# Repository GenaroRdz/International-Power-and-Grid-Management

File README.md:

# ⚡ Design and Implementation of Mechatronic Systems: ECU Test Bench

This repository contains all the code, hardware schematics, and assets used for the class **Design and Implementation of Mechatronic Systems**. 

The core of this project is a **High-Current Load Controller (ECU Test Bench)** designed to safely simulate, control, and monitor high-power loads (12V/5A) using solid-state switching and a custom Python Graphical User Interface (GUI).

---# ⚡ Automated HIL Power & Grid Management Unit

> **Solid-State ECU Test Bench for Automotive Hardware-In-the-Loop (HIL) Validation**

This repository contains the firmware, host software, hardware schematics, and testing assets developed for the *Design and Implementation of Mechatronic Systems* engineering capstone. 

The core of this project is a **High-Current Power Management Unit (PMU)** designed to safely automate the power cycling, control, and real-time monitoring of automotive Electronic Control Units (ECUs). By replacing traditional mechanical relays and manual resets with a fully automated, VISA-compliant Python GUI and a solid-state switching matrix, this system provides a robust framework for continuous ECU stress-testing.

## 📋 System Architecture

The architecture relies on a strict separation of concerns across three layers, safely isolating the low-voltage logic control (3.3V) from the raw automotive power stage (12V) using galvanic isolation.

1. **Host Layer (PC / Python):** A robust GUI that manages serial connection watchdogs, visualizes live telemetry on an oscilloscope, and parses automation scripts (e.g., `LOOP 10`, `DELAY 100`) into single-line SCPI/VISA string commands (`*IDN?`, `ECU1_BAT ON`).
2. **Control Layer (ESP32 / MicroPython):** An asynchronous event-driven firmware (`asyncio`) that parses commands, manages GPIO logic, polls I2C sensors, and controls the SPI CAN bus simultaneously without blocking the main loop.
3. **Hardware Layer (Custom PCB):** A 12-channel power delivery matrix protecting the logic domain from automotive 12V inrush currents and inductive spikes.

## 🚀 Key Features & Core Components

* **Solid-State Power Matrix:** Independent 12V/5A control over Battery (BAT), Accessory (ACC), and Ignition (IGN) lines across 4 distinct ECU channels.
  * *Component:* P-Channel Power MOSFETs (IRF4905) driven by PC817 Optocouplers.
* **Real-Time I2C Telemetry:** Closed-loop monitoring of voltage, current, and power consumption per channel using custom bare-metal I2C drivers.
  * *Component:* INA226 digital power monitors with ultra-low 0.01Ω shunt resistors and hardware-configured I2C addresses.
* **CAN Bus Integration:** SPI-driven CAN controller integration for broadcast messaging, ECU node-health supervision, and live traffic monitoring via the GUI.
  * *Component:* MCP2515 CAN Controller + TJA1050 Transceiver.
* **Automated Sequencer:** Custom scripting engine allowing the execution of complex testing vectors (e.g. stress tests) directly from `.txt` files.

## 📂 Repository Structure

* `/Firmware`: MicroPython scripts for the ESP32 (main asynchronous loop, custom `INA226.py` and `mcp2515.py` register-level drivers, command parser).
* `/Software`: Python GUI application (Tkinter), live scope plotting, CAN monitor, and serial management.
* `/Hardware`: KiCad schematics, wiring diagrams, LTspice validation simulations (`.asc`, `.model`), and Bill of Materials (BOM).
* `/Tests`: Example sequence `.txt` files for automated stress testing (e.g., `COMPLETE Test.txt`).
* `/Docs`: Final Technical Report, architecture diagrams, and component datasheets.

## 🛠️ Setup and Installation

### 1. Hardware Assembly
Assemble the physical circuit following the schematics provided in the `/Hardware` folder.
> ⚠️ **Safety Warning:** This system handles cumulative currents capable of exceeding 15A during inrush events. Ensure the use of appropriate gauge wiring (AWG 16 minimum) for the 12V power bus, use proper thermal dissipation techniques, and include a master inline fuse & kill-switch before the MOSFET array.

### 2. Firmware (ESP32)
1. Flash the ESP32 microcontroller with the latest MicroPython firmware.
2. Upload all python scripts from the `/Firmware` folder to the board using tools like Thonny IDE or `mpremote`.
3. The board will automatically execute `main.py` on boot, initialize the SPI/I2C buses, and await serial commands at `115200` bauds.

### 3. Software (Python GUI)
The host control interface requires **Python 3.13.x**. Navigate to the software folder and install the required dependencies:

```bash
cd Software
pip install -r requirements.txt
python main.py
```
## 📋 System Architecture

The project is modularly designed, safely isolating the low-voltage logic control (3.3V) from the raw power stage (12V) using optocouplers. 

### Core Components:
* **Microcontroller:** ESP32 running MicroPython.
* **Power Switching:** P-Channel Power MOSFET (IRF4905).
* **Current/Voltage Monitoring:** INA226 (I2C) with an ultra-low shunt resistor.
* **Isolation:** PC817 Optocoupler.
* **Simulated Load:** 120 Ohms Resistors. (in total 12 Resistors ~1.2A drawn).

---

## 📂 Repository Structure

* `/firmware`: MicroPython scripts for the ESP32 (I2C sensor reading, PWM/Digital control).
* `/software`: Python GUI application for remote monitoring and control.
* `/hardware`: Circuit schematics, wiring diagrams, and LTspice simulations (`.asc`, `.model`).
* `/docs`: Final Report, technical documentation and component datasheets (INA226, IRF4905, etc.).

---

## 🛠️ Setup and Installation

### 1. Hardware Assembly
Assemble the physical circuit following the schematics provided in the `/hardware` folder. 
> ⚠️ **Safety Warning:** This system handles currents <= 5A. Ensure the use of appropriate gauge wiring (AWG 16 minimum) for the power stage and include a master kill-switch before the MOSFET array.

### 2. Firmware (ESP32)
Flash the ESP32 with the latest MicroPython firmware. Upload the scripts from the `/firmware` folder to the board using tools like Thonny IDE or `mpremote`.

### 3. Software (Python GUI)
The control interface requires **Python 3.13.xx**. Navigate to the software folder and install the required dependencies:

```bash
cd software
pip install -r requirements.txt
python main.py

Authors:
Genaro Rodríguez Garza - A00831640 
Juan Pablo Carrasco Ferra Martínez - A01252910 
Eduardo de la Rosa Flores - A01039969 
Kleber Andres Molina Yepez - A00838725 
Jose Joaquin Rodriguez Cisneros - A00833104

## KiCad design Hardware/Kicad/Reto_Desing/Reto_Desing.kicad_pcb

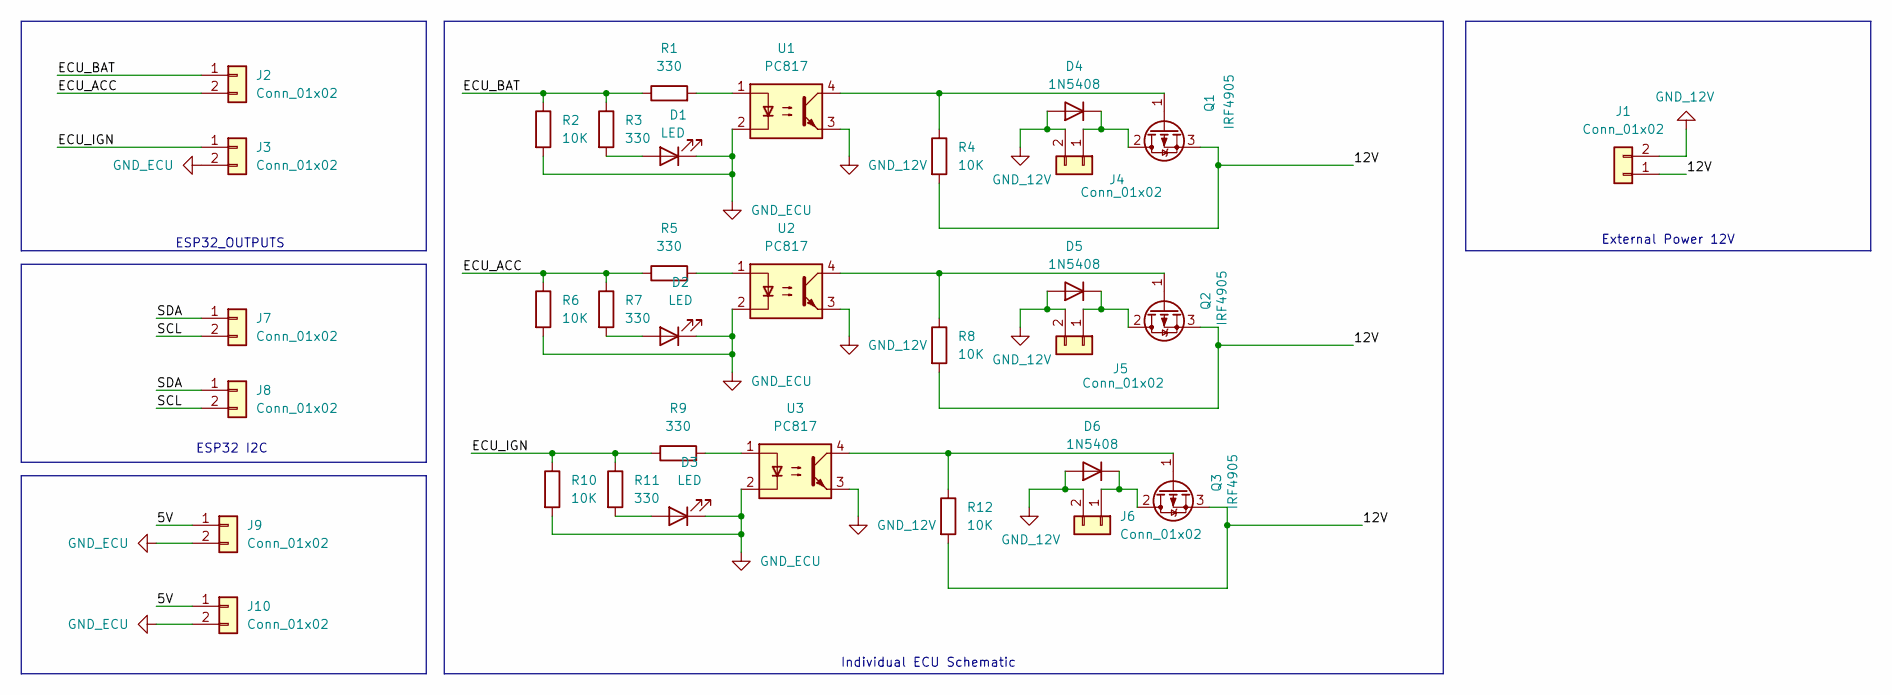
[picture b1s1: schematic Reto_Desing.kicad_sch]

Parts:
D1, D2, D3: LED; LED_D5.0mm
D4, D5, D6: 1N5408; D_DO-201AD_P15.24mm_Horizontal
J1, J2, J3, J4, J5, J6, J7, J8, J9, J10: Conn_01x02; JWT_A3963_1x02_P3.96mm_Vertical
Q1, Q2, Q3: IRF4905; TO-220-3_Vertical
R1, R3, R5, R7, R9, R11: 330; R_Axial_DIN0207_L6.3mm_D2.5mm_P10.16mm_Horizontal
R2, R4, R6, R8, R10, R12: 10K; R_Axial_DIN0207_L6.3mm_D2.5mm_P10.16mm_Horizontal
U1, U2, U3: PC817; DIP-4_W7.62mm

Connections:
/5V: J9.1, J10.1
/12V: J1.1, Q1.3 (S), Q2.3 (S), Q3.3 (S), R4.2, R8.2, R12.2
/ECU_ACC: J2.2, R5.1, R6.1, R7.1
/ECU_BAT: J2.1, R1.1, R2.1, R3.1
/ECU_IGN: J3.1, R9.1, R10.1, R11.1
/SCL: J7.2, J8.2
/SDA: J7.1, J8.1
GND_12V: D4.2 (A), D5.2 (A), D6.2 (A), J1.2, J4.2, J5.2, J6.2, U1.3, U2.3, U3.3
GND_ECU: D1.1 (K), D2.1 (K), D3.1 (K), J3.2, J9.2, J10.2, R2.2, R6.2, R10.2, U1.2, U2.2, U3.2
unnamed: D1.2 (A), R3.2
unnamed: D2.2 (A), R7.2
unnamed: D3.2 (A), R11.2
unnamed: D4.1 (K), J4.1, Q1.2 (D)
unnamed: D5.1 (K), J5.1, Q2.2 (D)
unnamed: D6.1 (K), J6.1, Q3.2 (D)
unnamed: Q1.1 (G), R4.1, U1.4
unnamed: Q2.1 (G), R8.1, U2.4
unnamed: Q3.1 (G), R12.1, U3.4
unnamed: R1.2, U1.1
unnamed: R5.2, U2.1
unnamed: R9.2, U3.1

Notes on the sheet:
ESP32_OUTPUTS
Individual ECU Schematic
External Power 12V
ESP32 I2C

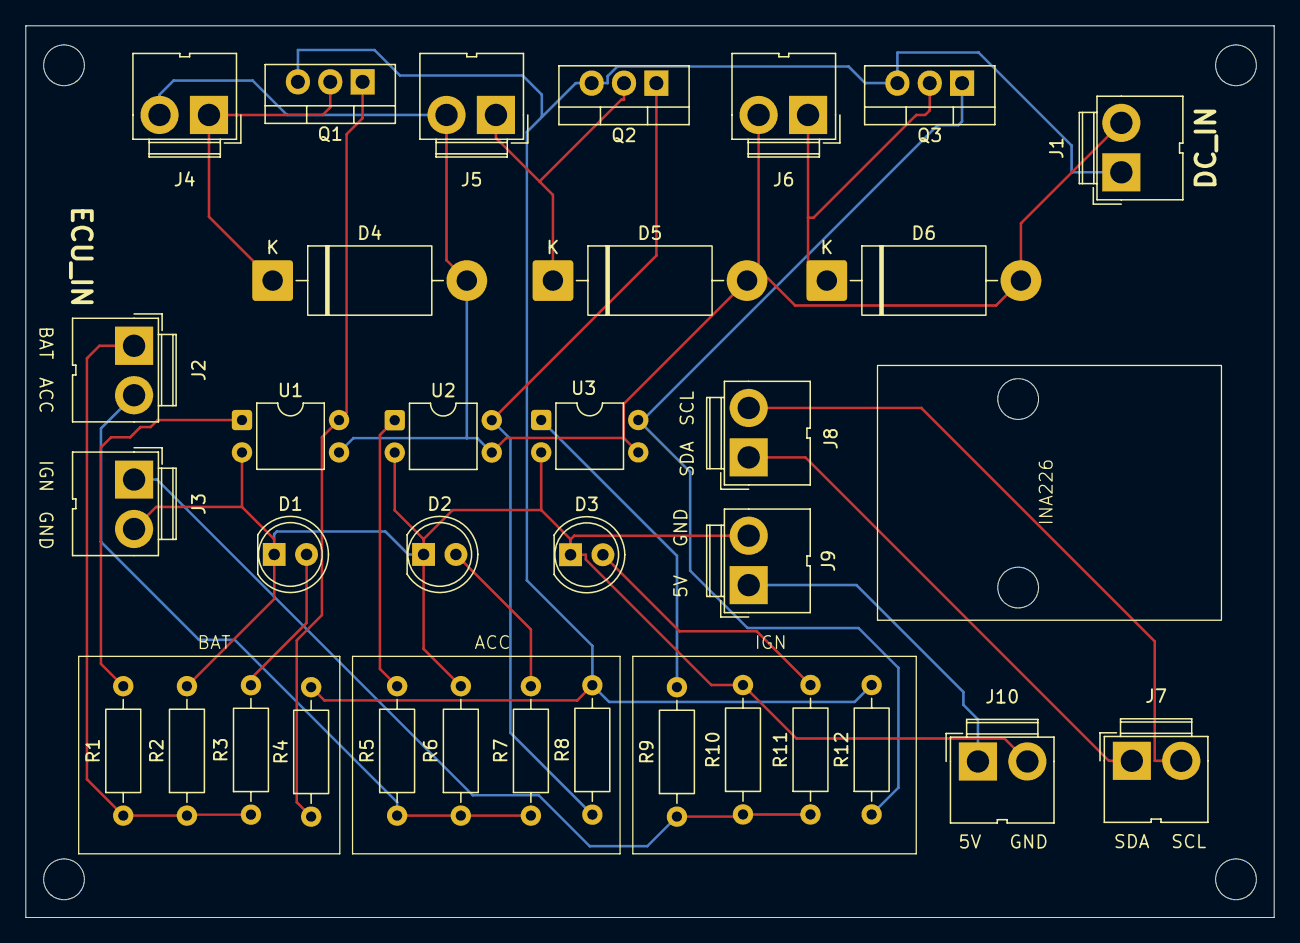
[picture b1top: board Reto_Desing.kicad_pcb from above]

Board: 2 copper layers, 98.0 x 70.0 mm, 35 parts (0 on the bottom side), 21 nets.

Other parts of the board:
INA226: INA226

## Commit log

2026-03-27 Add-CNN-neuronal-network
2026-03-29 Last code using in the document
2026-04-15 Folder cleaning
2026-04-20 GUI_ECU
2026-04-20 Update README with Python version details
    Added Python version information for the project.
2026-04-21 Create /docs
2026-04-22 Create /LTspice_simulations
2026-04-22 Uploaded LTSpice files
    Simulations and other documents where added
2026-04-22 Circuit Image (pdf) upload
2026-04-22 requirements.txt and .gitignore update
2026-04-22 Update .gitignore with /venv
2026-05-11 SPI2CAN and mcp2515 file added
2026-05-13 INA226.py Added
2026-05-16 INA226.py chages
2026-05-23 updating docs
2026-05-27 Kicad added
2026-05-28 GUI Scope Update
2026-05-28 status_bar update
2026-05-29 GUI V2 Update
2026-05-29 Return to functional GUI
2026-05-30 GUI_ECU Async.py
2026-05-30 Async New_device_connection_2.py
2026-05-30 Async INA226.py
2026-05-30 async functions.py
2026-05-30 Async main.py
2026-05-30 Async Correction
2026-05-30 Scope_Scales_Colors
2026-05-30 INA Channels
2026-05-30 Color Change
2026-05-30 Color_offline
2026-06-02 GUI COM Settings Full Window
2026-06-08 Pins_changed Thonny
2026-06-08 test commit
2026-06-08 CAN_Communication_Micropython
2026-06-09 GUI CAN Monitor
2026-06-09 micropython CAN GUI code
2026-06-09 ECU Receiver
2026-06-09 Monitor Error Handling
2026-06-09 Micropython CAN mod
2026-06-09 Slow CAN fixed
2026-06-11 Latest_Code
2026-06-11 Latest_Code _ Working
2026-06-11 Kicad new desing
2026-06-11 feature: New Terminal Testing Window
2026-06-11 .gitignore update
2026-06-11 Update README.md
    Updated Readme
2026-06-11 chore: Remove folder
2026-06-15 Update README.md
    Added names
